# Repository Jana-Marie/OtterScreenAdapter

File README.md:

# OtterScreenAdapter

It turns out that modern screens/panels like the LP097QX1-SPA1 from LG have a eDP interface, which is only DP (DisplayPort) but without a standard connector. You can buy such a screen for ~40€ and with the OtterScreenAdapter (part cost: ~10€) you can convert it into an external 2048x1536px monitor.

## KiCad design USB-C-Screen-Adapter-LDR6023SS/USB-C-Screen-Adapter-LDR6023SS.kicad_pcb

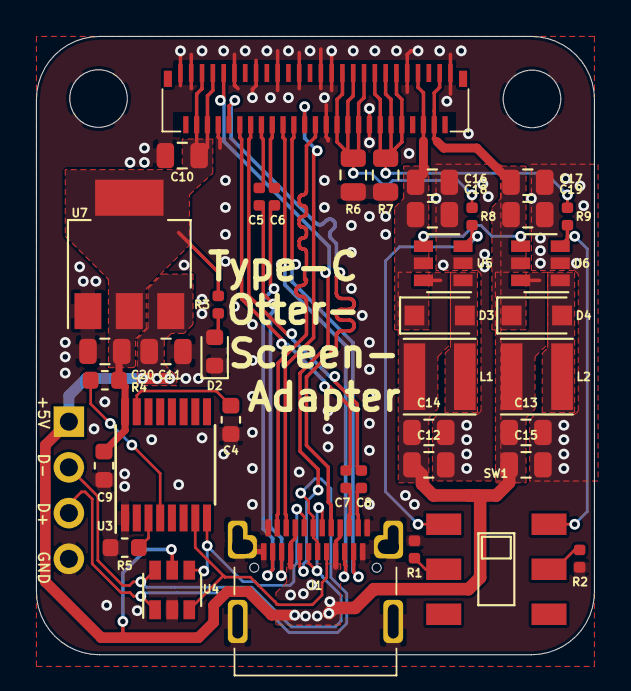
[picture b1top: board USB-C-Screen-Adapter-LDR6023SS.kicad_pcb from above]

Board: 2 copper layers, 31.0 x 34.3 mm, 42 parts (0 on the bottom side), 36 nets.

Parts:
C4, C9: 100n; C_0603_1608Metric
C5, C6, C7, C8: 100n; C_0402_1005Metric
C10, C11, C12, C13, C14, C15, C16, C17, C18, C19, C20: 2.2uF; C_0805_2012Metric
D2: LED; LED_0603_1608Metric
D3, D4: SM4007PL; D_SOD-123F
H1, H2: MountingHole_Pad; MountingHole_3.2mm_M3
J1: USB_C_Receptacle; USB_C_24P_SMD
J2: USB; PinHeader_1x04_P2.54mm_Vertical
L1, L2: 22uH; L_Taiyo-Yuden_MD-4040
R1, R2, R3, R8, R9: 1k; R_0402_1005Metric
R4, R5: 10k; R_0603_1608Metric
R6, R7: 1.6; R_0805_2012Metric
SW1: BRIGHTNESS; K3-2235S-K1
U2: 5022505191
U3: LDR6023SS; TSSOP-16_4.4x5mm_P0.65mm
U4: USBLC6-4; SOT-23-6
U5, U6: SY7200AABC; SOT-23-6
U7: AMS1117-3.3; SOT-223-3_TabPin2

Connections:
+3V3: C9.1, C10.1, C20.1, R3.2, R4.2, U2.4, U2.5, U2.6, U2.7, U3.16, U7.2
+5V: C11.1, C12.1, C13.1, C14.1, C15.1, J1.A4, J1.A9, J1.B4, J1.B9, J2.1, L1.1, L2.1, U4.5, U5.6, U6.6, U7.3
/_L0_N: C7.2, J1.A10
/_L0_P: C8.2, J1.A11
/_L1_N: C5.2, J1.B10
/_L1_P: C6.2, J1.B11
AUX_N: J1.A8, U2.10
AUX_P: J1.B8, U2.9
CC1: J1.A5, U3.8, U4.4
CC2: J1.B5, U3.7, U4.3
GND: C4.2, C9.2, C10.2, C11.2, C12.2, C13.2, C14.2, C15.2, C16.2, C17.2, C18.2, C19.2, C20.2, D2.1, H1.1, H2.1, J1.A1, J1.A12, J1.B1, J1.B12, J1.S1, J2.4, R1.1, R2.1, R5.2, R6.2, R7.2, U2.1, U2.3, U2.8, U2.11, U2.15, U2.19, U2.23, U2.27, U2.28, U2.29, U2.36, U2.43, U2.51, U3.1, U4.2, U5.2, U6.2, U7.1
L0_N: C7.1, U2.12
L0_P: C8.1, U2.14
L1_N: C5.1, U2.16
L1_P: C6.1, U2.18
L2_N: J1.B3, U2.20
L2_P: J1.B2, U2.22
L3_N: J1.A3, U2.24
L3_P: J1.A2, U2.26
LEDA1: C17.1, C19.1, D4.1, U2.48, U2.49, U6.5
LEDA2: C16.1, C18.1, D3.1, U2.45, U2.46, U5.5
LEDC1: R7.1, R9.2, U2.37, U2.38, U2.39, U2.40, U2.41, U2.42
LEDC1DIM: R9.1, SW1.4, U6.3
LEDC2: R6.1, R8.2, U2.30, U2.31, U2.32, U2.33, U2.34, U2.35
LEDC2DIM: R8.1, SW1.1, U5.3
unnamed: C4.1, U3.15
unnamed: D2.2, R3.1
unnamed: D3.2, L1.2, U5.1
unnamed: D4.2, L2.2, U6.1
unnamed: R1.2, SW1.2
unnamed: R2.2, SW1.5
unnamed: R4.1, U3.4
unnamed: R5.1, U3.3
PWM: U5.4, U6.4
USB_N: J1.A7, J1.B7, J2.2, U4.6
USB_P: J1.A6, J1.B6, J2.3, U4.1

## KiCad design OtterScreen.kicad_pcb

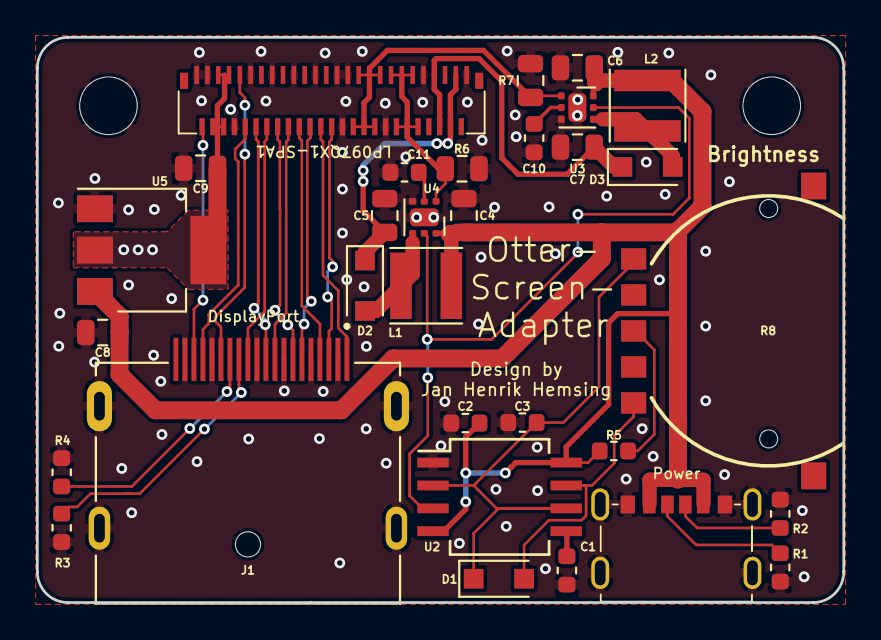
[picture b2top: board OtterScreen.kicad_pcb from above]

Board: 2 copper layers, 44.8 x 31.4 mm, 33 parts (0 on the bottom side), 31 nets.

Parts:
C1, C2: 100n; C_0603_1608Metric
C3: 1n; C_0603_1608Metric
C4, C6: 10uF; C_0805_2012Metric
C5, C7, C8, C9: 0.47uF; C_0805_2012Metric
C10, C11: 220nF; C_0603_1608Metric
D1: D; D_SOD-123F
D2, D3: SS34; D_SOD-123F
H1, H2: MountingHole_Pad; MountingHole_3.2mm_M3
J1: 47272-0001; MOLEX_47272-0001
J2: USB-C_Power
L1, L2: 22uH; L_Taiyo-Yuden_MD-4040
R1, R2: 5K1; R_0603_1608Metric
R3, R4: 0; R_0603_1608Metric
R5: 100; R_0603_1608Metric
R6, R7: 0.8; R_0805_2012Metric
R8: RK14J12R0A09
U1: 5022505191
U2: NE555; SO-8_5.3x6.2mm_P1.27mm
U3, U4: TPS61160A; WSON-6-1EP_2x2mm_P0.65mm_EP1x1.6mm
U5: AMS1117-3.3; SOT-223-3_TabPin2

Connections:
+3V3: C9.1, U1.4, U1.5, U1.6, U1.7, U5.2
+5V: C2.1, C4.1, C6.1, C8.1, J2.2, J2.5, L1.1, L2.1, R5.1, U2.4, U2.8, U3.6, U4.6, U5.3
AUX_N: J1.17, U1.10
AUX_P: J1.15, U1.9
GND: C1.2, C2.2, C3.2, C4.2, C5.2, C6.2, C7.2, C8.2, C9.2, C10.2, C11.2, H1.1, H2.1, J1.2, J1.5, J1.8, J1.11, J1.16, J1.19, J1.S1, J1.S2, J1.S3, J1.S4, J2.1, J2.6, J2.7, R1.2, R2.2, R3.2, R4.2, R6.2, R7.2, U1.1, U1.3, U1.8, U1.11, U1.15, U1.19, U1.23, U1.27, U1.28, U1.29, U1.36, U1.43, U1.51, U2.1, U3.3, U3.7, U4.3, U4.7, U5.1
HPD: J1.18, U1.2
L0_N: J1.10, U1.12
L0_P: J1.12, U1.14
L1_N: J1.7, U1.16
L1_P: J1.9, U1.18
L2_N: J1.4, U1.20
L2_P: J1.6, U1.22
L3_N: J1.1, U1.24
L3_P: J1.3, U1.26
LEDA1: C5.1, D2.1, U1.48, U1.49
LEDA2: C7.1, D3.1, U1.45, U1.46
LEDC1: R6.1, U1.37, U1.38, U1.39, U1.40, U1.41, U1.42, U4.1
LEDC2: R7.1, U1.30, U1.31, U1.32, U1.33, U1.34, U1.35, U3.1
unnamed: C1.1, U2.5
unnamed: C3.1, D1.1, R8.1, U2.2, U2.6
unnamed: C10.1, U3.2
unnamed: C11.1, U4.2
unnamed: D1.2, R8.2, U2.7
unnamed: D2.2, L1.2, U4.4
unnamed: D3.2, L2.2, U3.4
unnamed: J1.13, R3.1
unnamed: J1.14, R4.1
unnamed: J2.3, R1.1
unnamed: J2.4, R2.1
unnamed: R5.2, R8.3
PWM: U2.3, U3.5, U4.5

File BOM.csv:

"Id";"Designator";"Package";"Quantity";"Designation";"Supplier and ref";
1;"C10,C11";"C_0603_1608Metric";2;"220nF";;;
2;"U3,U4";"WSON-6-1EP_2x2mm_P0.65mm_EP1x1.6mm";2;"TPS61160A";;;
3;"H2,H1";"MountingHole_3.2mm_M3";2;"MountingHole_Pad";;;
4;"C8,C9,C7,C5";"C_0805_2012Metric";4;"0.47uF";;;
5;"U5";"SOT-223-3_TabPin2";1;"AMS1117-3.3";;;
6;"J1";"MOLEX_47272-0001";1;"47272-0001";;;
7;"U2";"SO-8_5.3x6.2mm_P1.27mm";1;"NE555";;;
8;"R8";"RK14J12R0A09";1;"RK14J12R0A09";;;
9;"R7,R6";"R_0805_2012Metric";2;"0.8";;;
10;"R5";"R_0603_1608Metric";1;"100";;;
11;"L2,L1";"L_Taiyo-Yuden_MD-4040";2;"22uH";;;
12;"D3,D2";"D_SOD-123F";2;"SS34";;;
13;"D1";"D_SOD-123F";1;"D";;;
14;"C6,C4";"C_0805_2012Metric";2;"10uF";;;
15;"C3";"C_0603_1608Metric";1;"1n";;;
16;"C2,C1";"C_0603_1608Metric";2;"100n";;;
17;"J2";"USB-C_Power";1;"USB-C_Power";;;
18;"R4,R3";"R_0603_1608Metric";2;"0";;;
19;"R2,R1";"R_0603_1608Metric";2;"5K1";;;
20;"U1";"5022505191";1;"5022505191";;;

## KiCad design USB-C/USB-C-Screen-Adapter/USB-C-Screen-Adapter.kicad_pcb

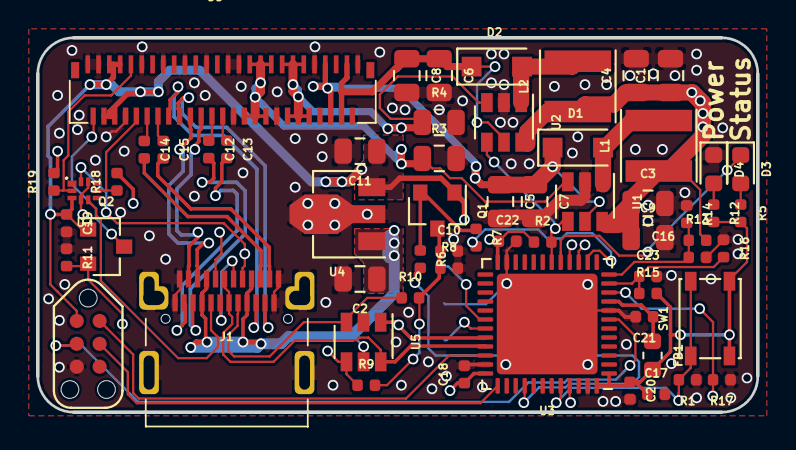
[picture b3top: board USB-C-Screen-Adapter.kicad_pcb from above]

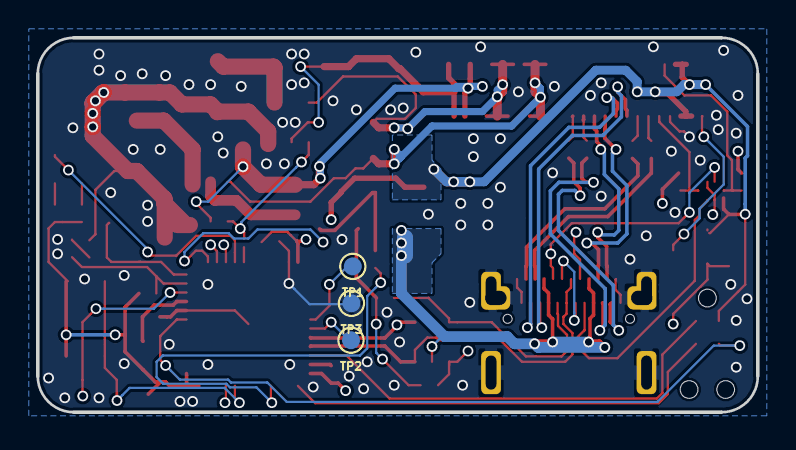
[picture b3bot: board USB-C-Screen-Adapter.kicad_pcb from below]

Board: 4 copper layers, 40.0 x 20.8 mm, 64 parts (3 on the bottom side), 51 nets.

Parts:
C1, C2, C3, C4, C5, C6, C7, C8, C9, C11: 2.2uF; C_0805_2012Metric
C10: 820p; C_0402_1005Metric
C12, C13, C14, C15, C16, C17, C18, C19, C20, C21, C22: 100n; C_0402_1005Metric
C23: 220n; C_0402_1005Metric
D1, D2: SM4007PL; D_SOD-123F
D3, D4: LED; LED_0603_1608Metric
FB1: FERRET; L_0603_1608Metric
J1: USB_C_Receptacle; USB_C_24P_SMD
L1, L2: 22uH; L_Taiyo-Yuden_MD-4040
P1: TC2030-CTX-Tag-Connect; TC2030
Q1, Q2: 2N7002; SOT-23
R1, R2, R8: 5k1; R_0402_1005Metric
R3, R4: 0.8; R_0805_2012Metric
R5, R12: 1k; R_0402_1005Metric
R6: 169; R_0402_1005Metric
R7: 75; R_0402_1005Metric
R9, R10, R18, R19: 0; R_0402_1005Metric
R11: 1M; R_0402_1005Metric
R13: 8k2; R_0402_1005Metric
R14: 1k5; R_0402_1005Metric
R15, R17: 24k; R_0402_1005Metric
R16: 4k7; R_0402_1005Metric
SW1: DFU; SW_SPST_PTS810
TP1: UART_TX; TestPoint_Pad_D1.0mm
TP2: UART_RX; TestPoint_Pad_D1.0mm
TP3: GND; TestPoint_Pad_D1.0mm
U1, U2: SY7200AABC; SOT-23-6
U3: STM32F072CBUx; QFN-48-1EP_7x7mm_P0.5mm_EP5.6x5.6mm
U4: AP2204R-3.3; SOT-89-3
U5: USBLC6-4; SOT-23-6
U6: 5022505191
U7: STG3684A; QFN10L

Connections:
+3V3: C11.1, C17.1, C18.1, C19.1, C20.1, C22.1, FB1.2, P1.1, Q1.1, Q2.1, R2.1, R5.2, R12.2, R15.2, SW1.2, U3.1, U3.24, U3.36, U3.48, U4.3, U6.4, U6.5, U6.6, U6.7, U7.3
+5V: C1.1, C2.1, C3.1, C4.1, C9.1, J1.A4, J1.A9, J1.B4, J1.B9, L1.1, L2.1, R13.2, U1.6, U2.6, U4.1, U5.5
/_L0_N: C14.2, J1.A10
/_L0_P: C15.2, J1.A11
/_L3_N: C12.2, J1.B10
/_L3_P: C13.2, J1.B11
AUX_N: R18.1, U6.10, U7.7
AUX_P: R19.1, U6.9, U7.2
CC1: J1.A5, R9.1, U5.4
CC2: J1.B5, R10.1, U5.3
CC_RX: R7.2, U3.14
CC_TX: R6.2, U3.40
DFU: R1.2, SW1.1, U3.44
GND: C1.2, C2.2, C3.2, C4.2, C5.2, C6.2, C7.2, C8.2, C9.2, C10.2, C11.2, C16.2, C17.2, C18.2, C19.2, C20.2, C21.2, C22.2, C23.2, D4.1, J1.A1, J1.A12, J1.B1, J1.B12, J1.S1, P1.5, R1.1, R3.2, R4.2, R8.2, R11.1, R14.1, R16.1, R17.1, TP3.1, U1.2, U2.2, U3.8, U3.23, U3.35, U3.47, U3.49, U4.2, U5.2, U6.1, U6.3, U6.8, U6.11, U6.15, U6.19, U6.23, U6.27, U6.28, U6.29, U6.36, U6.43, U6.51, U7.8
HPD: Q2.3, U6.2
L0_N: C14.1, U6.12
L0_P: C15.1, U6.14
L1_N: J1.B3, U6.16
L1_P: J1.B2, U6.18
L2_N: J1.A3, U6.20
L2_P: J1.A2, U6.22
L3_N: C12.1, U6.24
L3_P: C13.1, U6.26
LEDA1: C6.1, C8.1, D2.1, U2.5, U6.48, U6.49
LEDA2: C5.1, C7.1, D1.1, U1.5, U6.45, U6.46
LEDC1: R4.1, U2.3, U6.37, U6.38, U6.39, U6.40, U6.41, U6.42
LEDC2: R3.1, U1.3, U6.30, U6.31, U6.32, U6.33, U6.34, U6.35
NRST: P1.3, U3.7
unnamed: C10.1, Q1.3, R8.1, R9.2, R10.2
unnamed: D1.2, L1.2, U1.1
unnamed: D2.2, L2.2, U2.1
unnamed: D3.1, U3.17
unnamed: D3.2, R5.1
unnamed: D4.2, R12.1
unnamed: Q1.2, R6.1, R7.1
unnamed: TP1.1, U3.30
unnamed: TP2.1, U3.31
PWM: R2.2, U1.4, U2.4, U3.18
RXREF: C23.1, R15.1, R16.2, U3.11
SBU1: J1.A8, U7.10
SBU2: J1.B8, U7.5
SBU_ENABLE: R17.2, U3.10, U7.4, U7.9
STM_HPD: Q2.2, R11.2, U3.45
SWCLK: P1.4, U3.37
SWDIO: P1.2, U3.34
USB_N: J1.A7, J1.B7, U3.32, U5.1
USB_P: J1.A6, J1.B6, U3.33, U5.6
VBUS_SENSE: C16.1, R13.1, R14.2, U3.12
VDDA: C21.1, FB1.1, U3.9
_DP_AUX_N: R18.2, U3.15
_DP_AUX_P: R19.2, U3.16

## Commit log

2019-07-22 added gitignore
2019-08-12 updated files
2019-09-03 fixed bugs, added ams1117
2019-09-24 added new images
2019-09-24 removed old files
2019-09-24 added bom
2019-09-27 updated bom
2019-09-27 removed zip
2019-09-28 Create LICENSE
2019-10-07 add .pdf of schematic and layout
2019-10-07 added USB-C version
2019-10-08 redone layout
2019-10-08 finalized layout
2019-10-08 moved files, finalized silkscreen, added gerber
2019-10-08 moved files
2019-12-16 added new usb-c adapter
2019-12-16 updated schematic
2019-12-21 added gitignore and submodules
2019-12-21 updated layout
2019-12-21 fixed otter-screen-adapter, added gerber
2019-12-22 updated gerber
2019-12-22 removed old gerber
